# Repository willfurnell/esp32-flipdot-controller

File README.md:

# `esp32-flipdot-controller`

## Replacement controller for Hannover Flipdot Displays

This is a fork of the original https://github.com/themainframe/esp32-flipdot-controller, but is designed to allow for more than one panel (my display has three), and works with the Platform.IO build, and Arduino ecosystems.

It currently gets the time from an NTP server and displays it. The code obviosuly needs more work, but it's good enough for now. 

Also included in this repository are KiCad schematics for my version of the PCB, which has hardware (but not yet software) support for the built in LED strip and other personal customisations.

Based on the [blog post on damow.net](https://damow.net/fun-with-flip-dot-displays/)!

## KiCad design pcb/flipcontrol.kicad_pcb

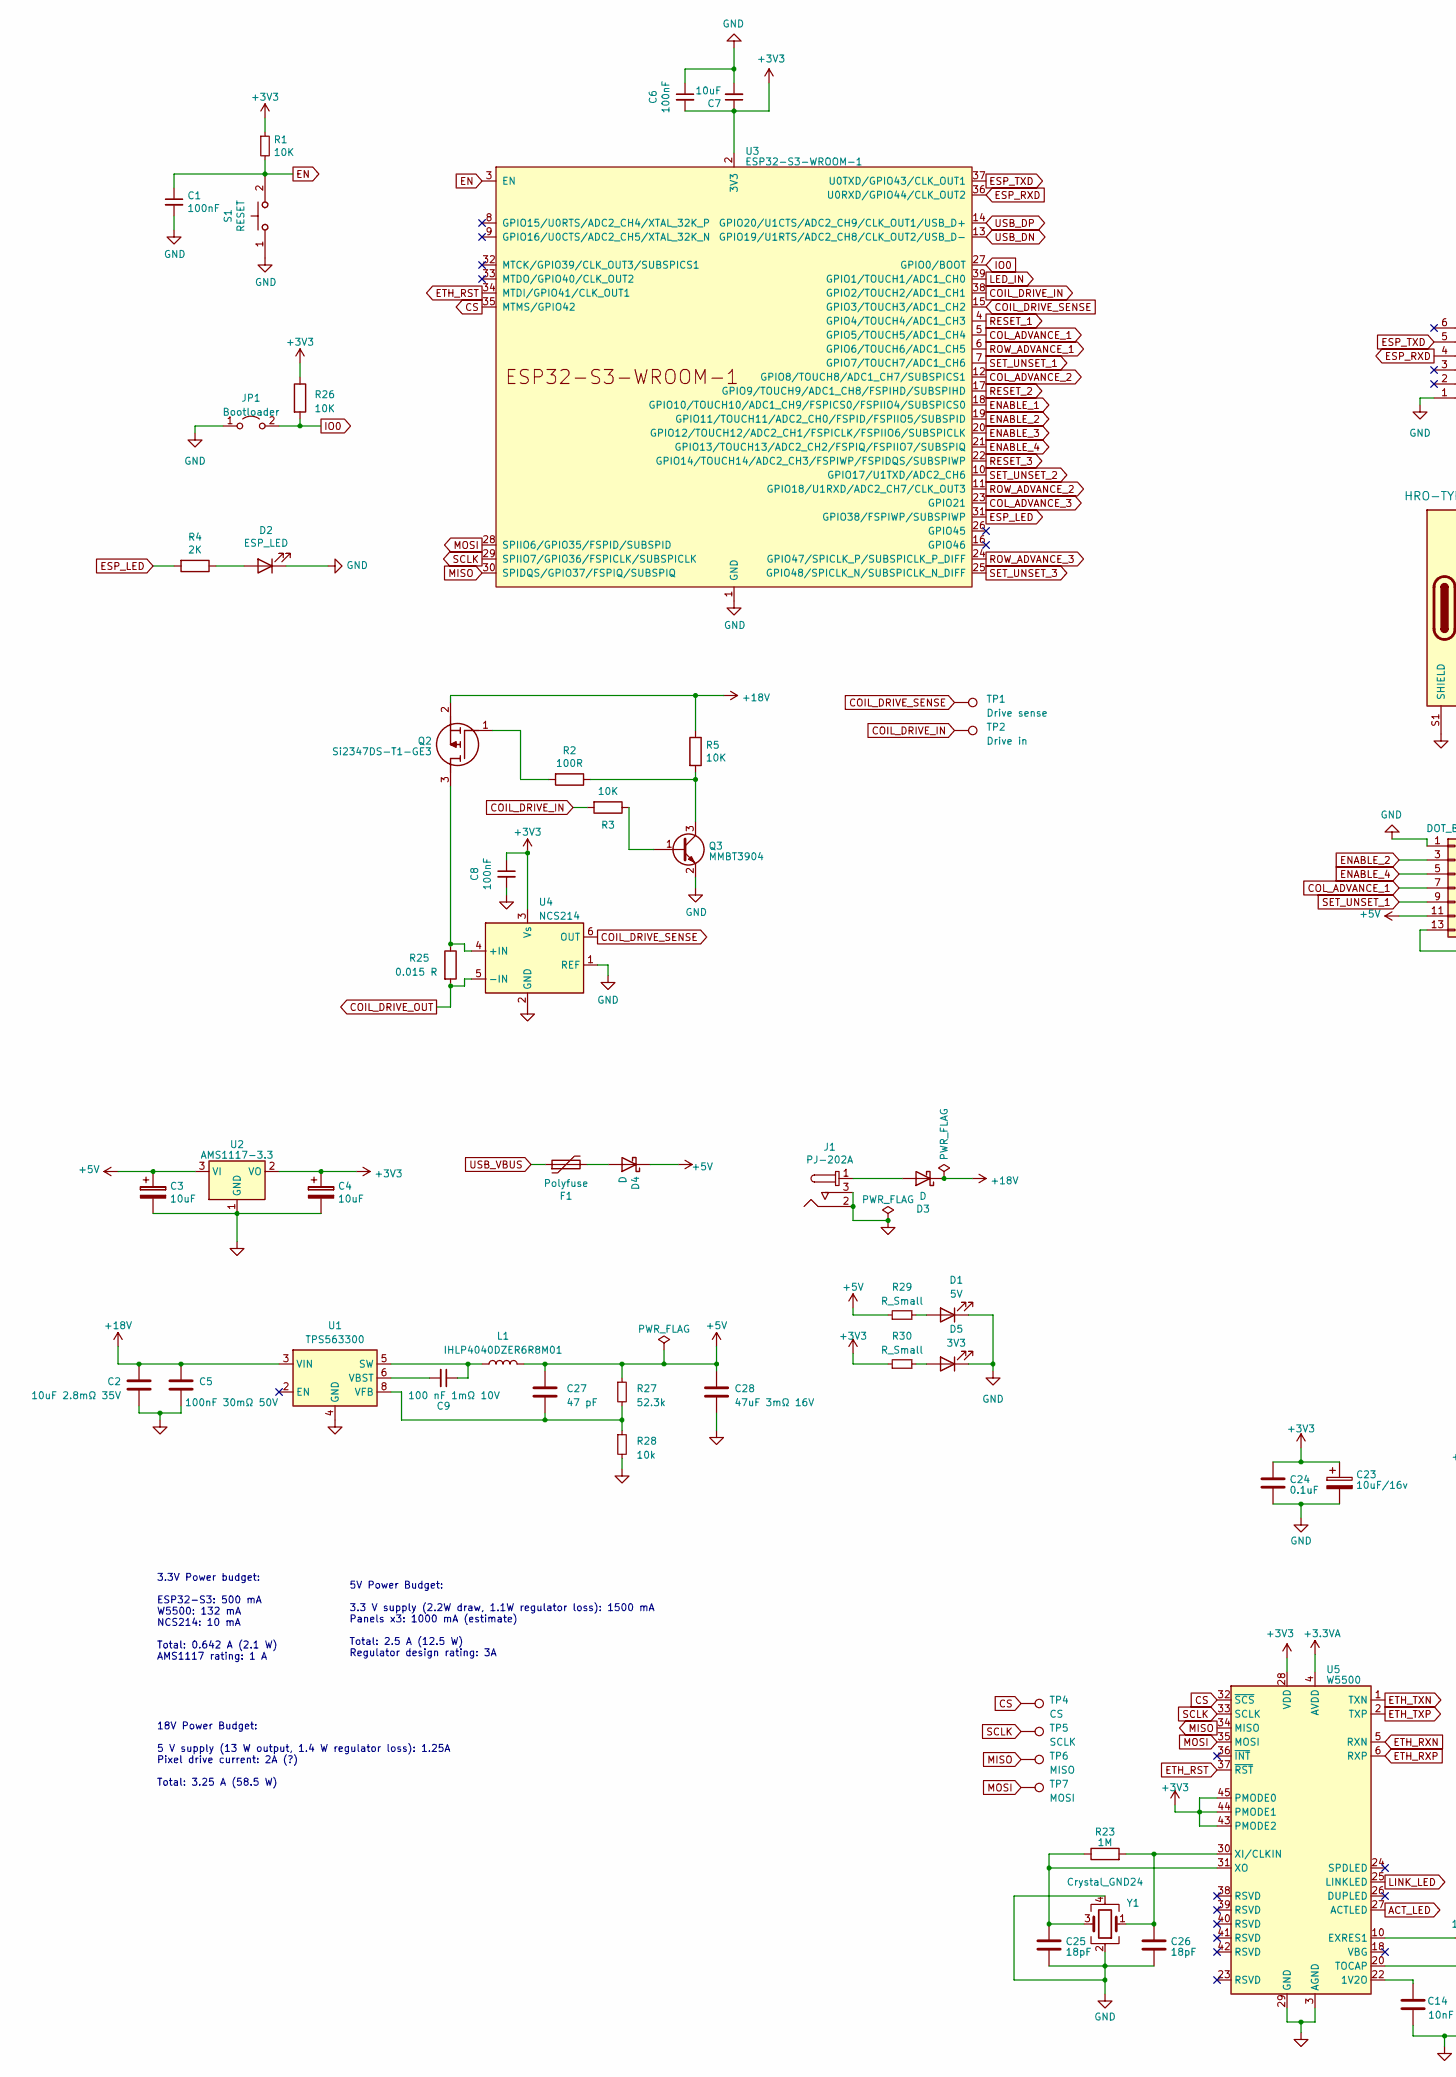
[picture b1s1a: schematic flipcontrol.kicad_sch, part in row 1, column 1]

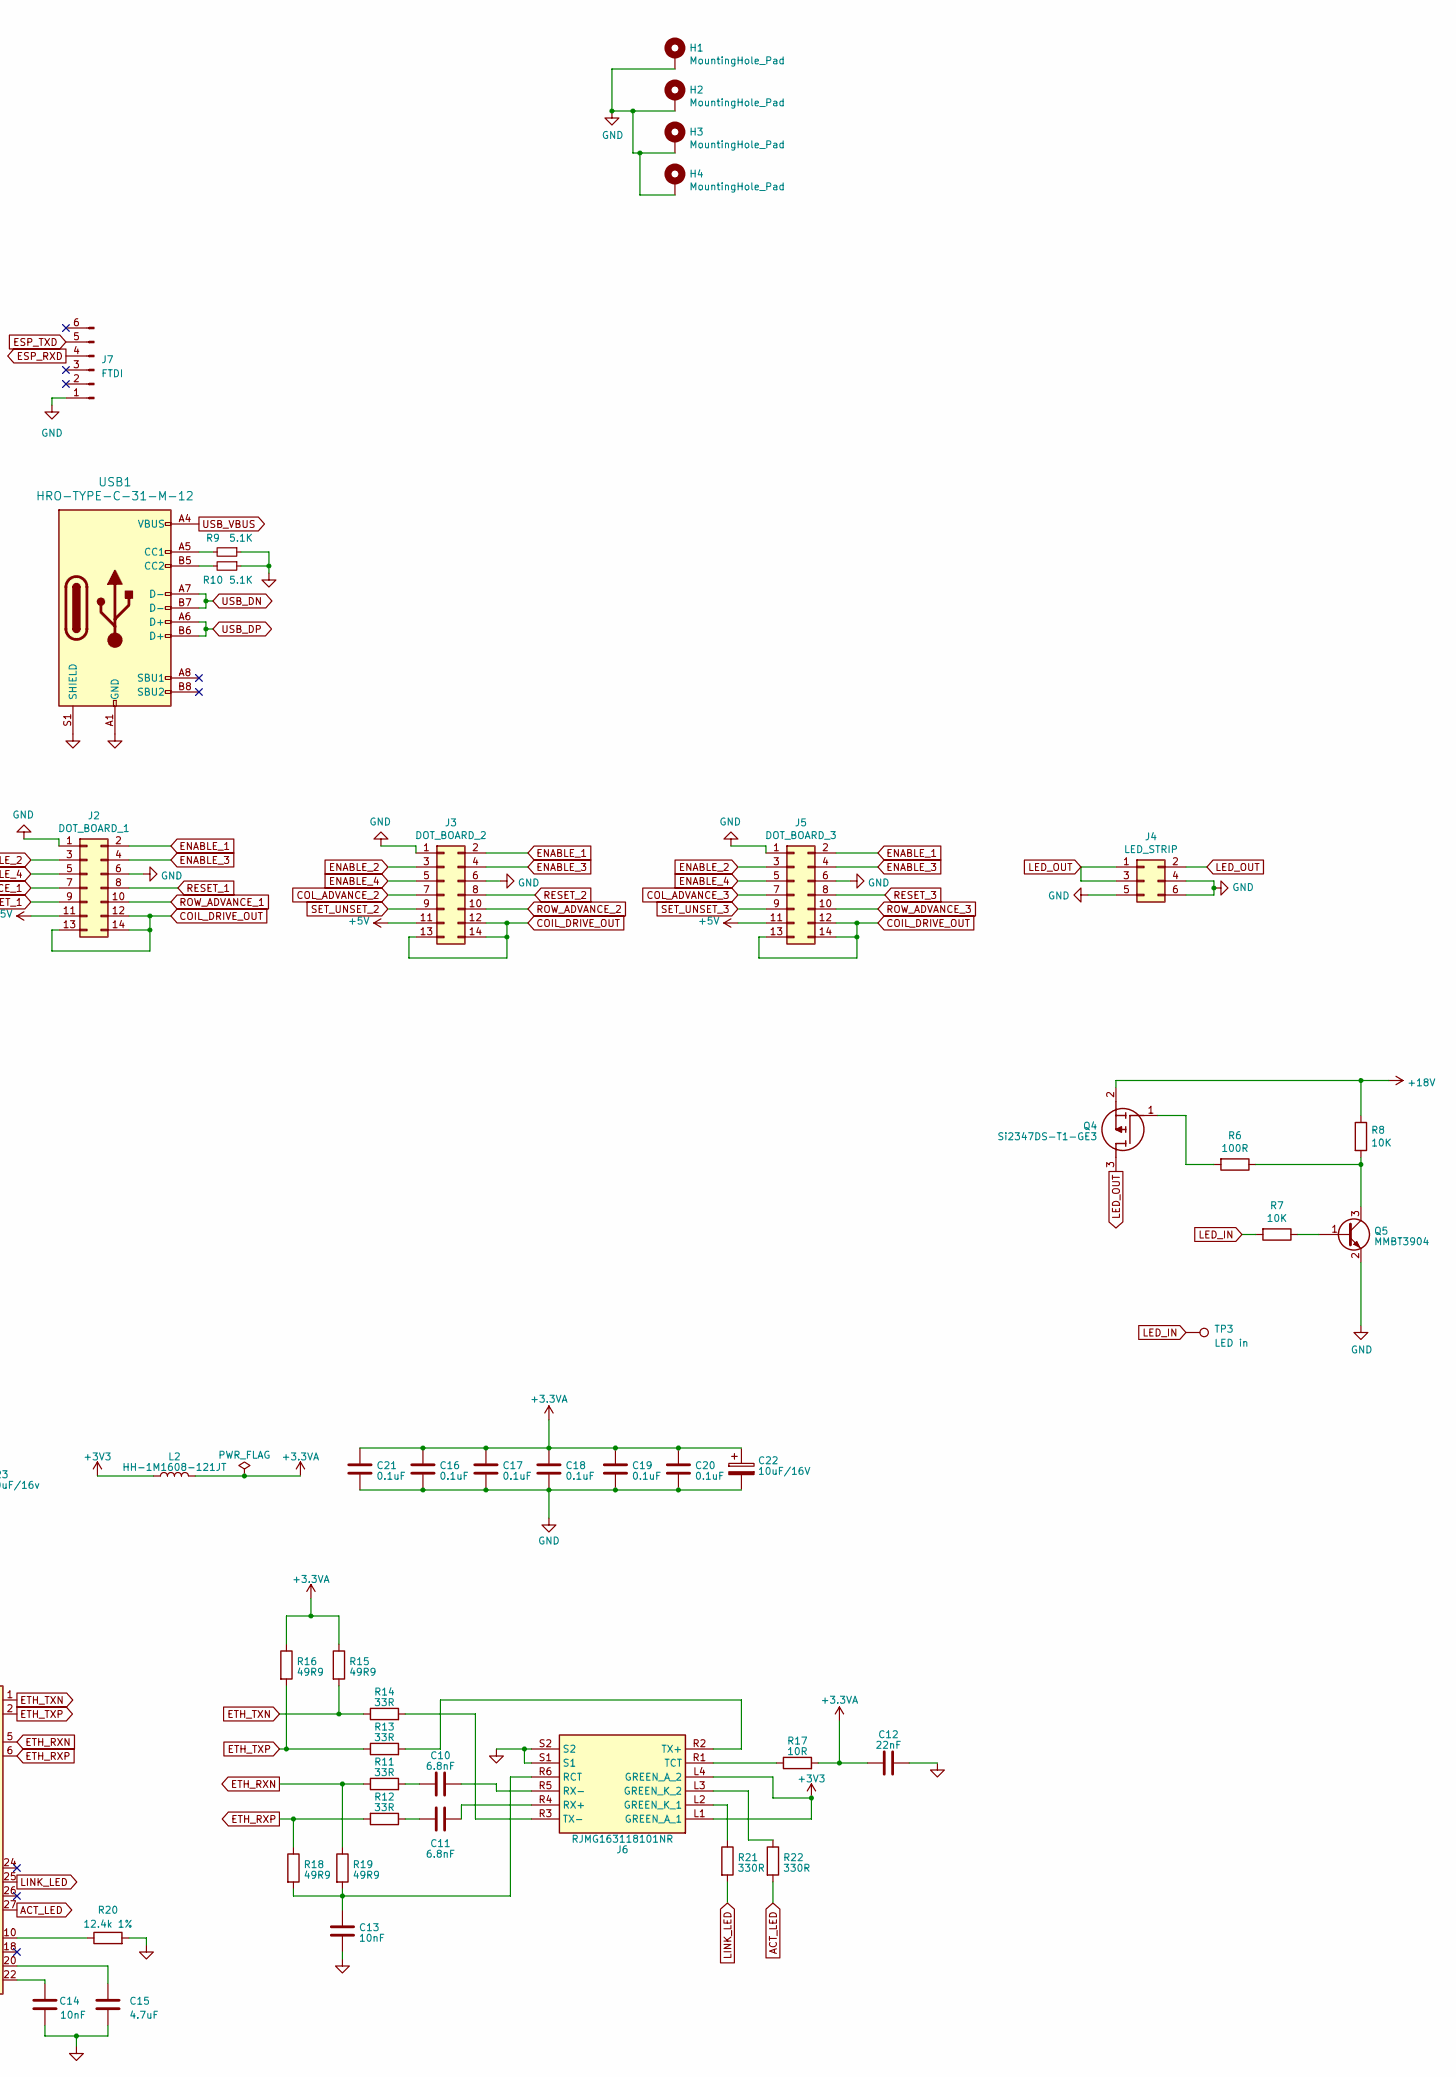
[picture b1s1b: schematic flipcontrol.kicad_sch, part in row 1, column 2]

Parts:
C1, C6, C8: 100nF; C_0805_2012Metric
C2: 10uF 2.8mΩ 35V; C_0805_2012Metric
C3, C4, C7: 10uF; C_0805_2012Metric
C5: 100nF 30mΩ 50V; C_0805_2012Metric
C9: 100 nF 1mΩ 10V; C_0805_2012Metric
C10, C11: 6.8nF; C_0805_2012Metric
C12: 22nF; C_0805_2012Metric
C13, C14: 10nF; C_0805_2012Metric
C15: 4.7uF; C_0805_2012Metric
C16, C17, C18, C19, C20, C21, C24: 0.1uF; C_0805_2012Metric
C22: 10uF/16V; C_0805_2012Metric
C23: 10uF/16v; C_0805_2012Metric
C25, C26: 18pF; C_0805_2012Metric
C27: 47 pF; C_0805_2012Metric
C28: 47uF 3mΩ 16V; C_1210_3225Metric
D1: 5V; LED_0805_2012Metric
D2: ESP_LED; LED_0805_2012Metric
D3, D4: D; D_SOD-123
D5: 3V3; LED_0805_2012Metric
F1: Polyfuse; Fuse_1206_3216Metric
H1, H2, H3, H4: MountingHole_Pad; MountingHole_5.3mm_M5_Pad
J1: PJ-202A; Barrel_Jack_5.5mmODx2.1mmID_PJ-202A; MPN PJ-202A; Digi-Key_PN CP-202A-ND
J2: DOT_BOARD_1; IDC-Header_2x07_P2.54mm_Vertical
J3: DOT_BOARD_2; IDC-Header_2x07_P2.54mm_Vertical
J4: LED_STRIP; IDC-Header_2x03_P2.54mm_Vertical
J5: DOT_BOARD_3; IDC-Header_2x07_P2.54mm_Vertical
J6: RJMG163118101NR; Manufacturer_Part_Number RJMG163118101NR; Mouser Part Number 523-RJMG163118101NR
J7: FTDI; PinHeader_1x06_P2.54mm_Vertical
JP1: Bootloader; Jumper_Tin_P5.32mm
L1: IHLP4040DZER6R8M01; L_Vishay_IHLP-4040
L2: HH-1M1608-121JT; L_0805_2012Metric
Q2, Q4: Si2347DS-T1-GE3; SOT95P237X112-3N; Manufacturer_Part_Number Si2347DS-T1-GE3; Mouser Part Number 78-SI2347DS-T1-GE3
Q3, Q5: MMBT3904; SOT-23
R1, R3, R5, R7, R8, R26: 10K; R_0805_2012Metric
R2, R6: 100R; R_0805_2012Metric
R4: 2K; R_0805_2012Metric
R9, R10: 5.1K; R_0805_2012Metric
R11, R12, R13, R14: 33R; R_0805_2012Metric
R15, R16, R18, R19: 49R9; R_0805_2012Metric
R17: 10R; R_0805_2012Metric
R20: 12.4k 1%; R_0805_2012Metric
R21, R22: 330R; R_0805_2012Metric
R23: 1M; R_0805_2012Metric
R25: 0.015 R; R_0805_2012Metric
R27: 52.3k; R_0805_2012Metric
R28: 10k; R_0805_2012Metric
R29, R30: R_Small; R_0805_2012Metric
S1: RESET; FSM2JRT; Mouser Part Number 506-FSM2JRT
TP1: Drive sense; TestPoint_Pad_D2.0mm
TP2: Drive in; TestPoint_Pad_D2.0mm
TP3: LED in; TestPoint_Pad_D2.0mm
TP4: CS; TestPoint_Pad_D2.0mm
TP5: SCLK; TestPoint_Pad_D2.0mm
TP6: MISO; TestPoint_Pad_D2.0mm
TP7: MOSI; TestPoint_Pad_D2.0mm
U1: TPS563300; SOT-583-8
U2: AMS1117-3.3; SOT-223-3_TabPin2
U3: ESP32-S3-WROOM-1
U4: NCS214; SOT-363_SC-70-6_Handsoldering
U5: W5500; LQFP-48_7x7mm_P0.5mm
USB1: HRO-TYPE-C-31-M-12; USB_C_Receptacle_HRO_TYPE-C-31-M-12
Y1: Crystal_GND24; Crystal_SMD_Abracon_ABM8G-4Pin_3.2x2.5mm

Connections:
+3.3VA: C12.1, C16.1, C17.1, C18.1, C19.1, C20.1, C21.1, C22.1, L2.2, R15.1, R16.1, R17.2, U5.4 (AVDD), U5.8 (AVDD), U5.11 (AVDD), U5.15 (AVDD), U5.17 (AVDD), U5.21 (AVDD)
+3V3: C4.1, C6.2, C7.1, C8.1, C23.1, C24.1, J6.L1 (GREEN_A_1), J6.L4 (GREEN_A_2), L2.1, R1.1, R26.1, R30.1, U2.2 (VO), U3.2 (3V3), U4.3 (Vs), U5.28 (VDD), U5.43 (PMODE2), U5.44 (PMODE1), U5.45 (PMODE0)
+5V: C3.1, C27.1, C28.1, D4.1 (K), J2.11, J3.11, J5.11, L1.2, R27.1, R29.1, U2.3 (VI)
+18V: C2.1, C5.1, D3.1 (K), Q2.2 (S), Q4.2 (S), R5.1, R8.1, U1.3 (VIN)
ACT_LED: R22.2, U5.27 (ACTLED)
COIL_DRIVE_IN: R3.2, TP2.1, U3.38 (GPIO2/TOUCH2/ADC1_CH1)
COIL_DRIVE_OUT: J2.12, J2.13, J2.14, J3.12, J3.13, J3.14, J5.12, J5.13, J5.14, R25.2, U4.5 (-IN)
COIL_DRIVE_SENSE: TP1.1, U3.15 (GPIO3/TOUCH3/ADC1_CH2), U4.6 (OUT)
COL_ADVANCE_1: J2.7, U3.5 (GPIO5/TOUCH5/ADC1_CH4)
COL_ADVANCE_2: J3.7, U3.12 (GPIO8/TOUCH8/ADC1_CH7/SUBSPICS1)
COL_ADVANCE_3: J5.7, U3.23 (GPIO21)
CS: TP4.1, U3.35 (MTMS/GPIO42), U5.32 (~SCS)
EN: C1.1, R1.2, S1.2, U3.3 (EN)
ENABLE_1: J2.2, J3.2, J5.2, U3.18 (GPIO10/TOUCH10/ADC1_CH9/FSPICS0/FSPIIO4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)
ENABLE_2: J2.3, J3.3, J5.3, U3.19 (GPIO11/TOUCH11/ADC2_CH0/FSPID/FSPIIO5/S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)
ENABLE_3: J2.4, J3.4, J5.4, U3.20 (GPIO12/TOUCH12/ADC2_CH1/FSPICLK/FSPIIO6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)
ENABLE_4: J2.5, J3.5, J5.5, U3.21 (GPIO13/TOUCH13/ADC2_CH2/FSPIQ/FSPIIO7/S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)
ESP_LED: R4.2, U3.31 (GPIO38/FSPIWP/SUBSPIWP)
ESP_RXD: J7.4, U3.36 (U0RXD/GPIO44/CLK_OUT2)
ESP_TXD: J7.5, U3.37 (U0TXD/GPIO43/CLK_OUT1)
ETH_RST: U3.34 (MTDI/GPIO41/CLK_OUT1), U5.37 (~RST)
ETH_RXN: R11.1, R19.1, U5.5 (RXN)
ETH_RXP: R12.2, R18.1, U5.6 (RXP)
ETH_TXN: R14.1, R15.2, U5.1 (TXN)
ETH_TXP: R13.1, R16.2, U5.2 (TXP)
GND: C1.2, C2.2, C3.2, C4.2, C5.2, C6.1, C7.2, C8.2, C12.2, C13.2, C14.1, C15.1, C16.2, C17.2, C18.2, C19.2, C20.2, C21.2, C22.2, C23.2, C24.2, C25.2, C26.2, C28.2, D1.1 (K), D2.1 (K), D5.1 (K), H1.1, H2.1, H3.1, H4.1, J1.2, J1.3, J2.1, J2.6, J3.1, J3.6, J4.4, J4.5, J4.6, J5.1, J5.6, J6.S1, J6.S2, J7.1, JP1.1 (A), Q3.2 (E), Q5.2 (E), R9.1, R10.1, R20.2, R28.2, S1.1, U1.4 (GND), U2.1 (GND), U3.1 (GND), U3.40 (GND), U3.41 (GND), U4.1 (REF), U4.2 (GND), U5.3 (AGND), U5.9 (AGND), U5.14 (AGND), U5.16 (AGND), U5.19 (AGND), U5.29 (GND), U5.48 (AGND), USB1.A1 (GND), USB1.A12 (GND), USB1.B1 (GND), USB1.B12 (GND), USB1.S1 (SHIELD), Y1.2, Y1.4
IO0: JP1.2 (B), R26.2, U3.27 (GPIO0/BOOT)
LED_IN: R7.2, TP3.1, U3.39 (GPIO1/TOUCH1/ADC1_CH0)
LED_OUT: J4.1, J4.2, J4.3, Q4.3 (D)
LINK_LED: R21.2, U5.25 (LINKLED)
MISO: TP6.1, U3.30 (SPIDQS/GPIO37/FSPIQ/SUBSPIQ), U5.34 (MISO)
MOSI: TP7.1, U3.28 (SPIIO6/GPIO35/FSPID/SUBSPID), U5.35 (MOSI)
unnamed: C10.2, R11.2
unnamed: C11.1, R12.1
unnamed: D1.2 (A), R29.2
unnamed: D2.2 (A), R4.1
unnamed: D3.2 (A), J1.1
unnamed: D4.2 (A), F1.2
unnamed: D5.2 (A), R30.2
unnamed: J6.L2 (GREEN_K_1), R21.1
unnamed: J6.L3 (GREEN_K_2), R22.1
unnamed: C13.1, J6.R6 (RCT), R18.2, R19.2
unnamed: C11.2, J6.R4 (RX+)
unnamed: C10.1, J6.R5 (RX-)
unnamed: J6.R1 (TCT), R17.1
unnamed: J6.R2 (TX+), R13.2
unnamed: J6.R3 (TX-), R14.2
unnamed: Q2.3 (D), R25.1, U4.4 (+IN)
unnamed: Q2.1 (G), R2.2
unnamed: Q3.1 (B), R3.1
unnamed: Q3.3 (C), R2.1, R5.2
unnamed: Q4.1 (G), R6.2
unnamed: Q5.1 (B), R7.1
unnamed: Q5.3 (C), R6.1, R8.2
unnamed: C9.1, L1.1, U1.5 (SW)
unnamed: C9.2, U1.6 (VBST)
unnamed: C27.2, R27.2, R28.1, U1.8 (VFB)
unnamed: C14.2, U5.22 (1V2O)
unnamed: R20.1, U5.10 (EXRES1)
unnamed: C15.2, U5.20 (TOCAP)
unnamed: C26.1, R23.2, U5.30 (XI/CLKIN), Y1.1
unnamed: C25.1, R23.1, U5.31 (XO), Y1.3
unnamed: R9.2, USB1.A5 (CC1)
unnamed: R10.2, USB1.B5 (CC2)
RESET_1: J2.8, U3.4 (GPIO4/TOUCH4/ADC1_CH3)
RESET_2: J3.8, U3.17 (GPIO9/TOUCH9/ADC1_CH8/FSPIHD/SUBSPIHD)
RESET_3: J5.8, U3.22 (GPIO14/TOUCH14/ADC2_CH3/FSPIWP/FSPIDQS/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)
ROW_ADVANCE_1: J2.10, U3.6 (GPIO6/TOUCH6/ADC1_CH5)
ROW_ADVANCE_2: J3.10, U3.11 (GPIO18/U1RXD/ADC2_CH7/CLK_OUT3)
ROW_ADVANCE_3: J5.10, U3.24 (GPIO47/SPICLK_P/SUBSPICLK_P_DIFF)
SCLK: TP5.1, U3.29 (SPIIO7/GPIO36/FSPICLK/SUBSPICLK), U5.33 (SCLK)
SET_UNSET_1: J2.9, U3.7 (GPIO7/TOUCH7/ADC1_CH6)
SET_UNSET_2: J3.9, U3.10 (GPIO17/U1TXD/ADC2_CH6)
SET_UNSET_3: J5.9, U3.25 (GPIO48/SPICLK_N/SUBSPICLK_N_DIFF)
USB_DN: U3.13 (GPIO19/U1RTS/ADC2_CH8/CLK_OUT2/USB_D-), USB1.A7 (D-), USB1.B7 (D-)
USB_DP: U3.14 (GPIO20/U1CTS/ADC2_CH9/CLK_OUT1/USB_D+), USB1.A6 (D+), USB1.B6 (D+)
USB_VBUS: F1.1, USB1.A4 (VBUS), USB1.A9 (VBUS), USB1.B4 (VBUS), USB1.B9 (VBUS)

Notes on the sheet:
3.3V Power budget: ESP32-S3: 500 mA W5500: 132 mA NCS214: 10 mA Total: 0.642 A (2.1 W) AMS1117 rating: 1 A
18V Power Budget: 5 V supply (13 W output, 1.4 W regulator loss): 1.25A Pixel drive current: 2A (?) Total: 3.25 A (58.5 W)
5V Power Budget: 3.3 V supply (2.2W draw, 1.1W regulator loss): 1500 mA Panels x3: 1000 mA (estimate) Total: 2.5 A (12.5 W) Regulator design rating: 3A

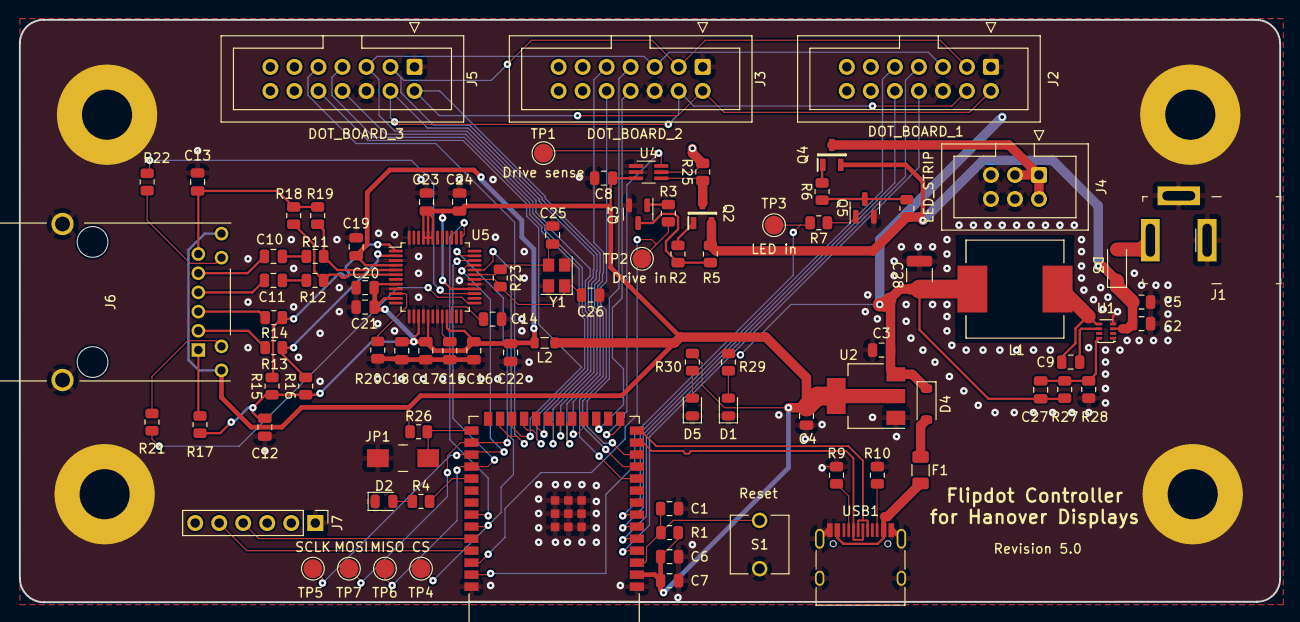
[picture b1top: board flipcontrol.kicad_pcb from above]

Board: 4 copper layers, 133.3 x 61.6 mm, 96 parts (0 on the bottom side), 77 nets.

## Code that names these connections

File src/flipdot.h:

#ifndef FLIPDOT_H
#define FLIPDOT_H

#include <stdint.h>
#include <stdbool.h>

// Dimensions of your display
//#define DOT_ROWS 8
//#define DOT_COLUMNS 84
//#define NUM_PANELS 3
//#define COLUMNS_PER_PANEL 28

// 32 x 16

#define DOT_ROWS 16
#define DOT_COLUMNS 96
#define NUM_PANELS 3
#define COLUMNS_PER_PANEL 32


// GPIO Pin Definitions
//#define PIN_ENABLE_1 GPIO_NUM_12
//#define PIN_ENABLE_2 GPIO_NUM_13
//#define PIN_ENABLE_3 GPIO_NUM_14
//#define PIN_ENABLE_4 GPIO_NUM_15
//#define PIN_COLUMN_ADVANCE GPIO_NUM_17
//#define PIN_RESET GPIO_NUM_16
//#define PIN_SET_UNSET GPIO_NUM_19
//#define PIN_ROW_ADVANCE GPIO_NUM_18
//#define PIN_COIL_DRIVE GPIO_NUM_21

#define PIN_ENABLE_1 GPIO_NUM_10
#define PIN_ENABLE_2 GPIO_NUM_11
#define PIN_ENABLE_3 GPIO_NUM_12
#define PIN_ENABLE_4 GPIO_NUM_13
#define PIN_COLUMN_ADVANCE GPIO_NUM_5
#define PIN_RESET GPIO_NUM_4
#define PIN_SET_UNSET GPIO_NUM_7
#define PIN_ROW_ADVANCE GPIO_NUM_6
#define PIN_COIL_DRIVE GPIO_NUM_2

#define GPIO_OUTPUT_PIN_SEL ((1ULL << PIN_ENABLE_1) | (1ULL << PIN_ENABLE_2) | (1ULL << PIN_ENABLE_3) | (1ULL << PIN_ENABLE_4) | (1ULL << PIN_COLUMN_ADVANCE) | (1ULL << PIN_RESET) | (1ULL << PIN_SET_UNSET) | (1ULL << PIN_ROW_ADVANCE) | (1ULL << PIN_COIL_DRIVE))

// Cycle count in 1 µS
#define CYCLES_PER_US 600

// Timings (µS)
#define PULSE_TIME_US 200
#define WAIT_TIME 1

// Types
typedef uint8_t dotboard_t[DOT_COLUMNS][DOT_ROWS];

// Public subs
void flipdot_init();
void write_dotboard(dotboard_t *dots, bool is_keyframe);

#endif

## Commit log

2020-10-11 Convert to platform.io
2020-10-11 Update to work with more than one panel (in this case three)
2020-10-11 Autoformat code for readability
2020-10-11 Allow configuration of display panels
2020-10-11 Add PCB files
2023-04-21 Update for Kicad 7, update some components
2023-04-22 Update schematic with newer parts
2023-04-22 Update PCB
2023-04-23 Update with latest schematic and board changes
2023-04-23 Update .gitignore with new KiCad bits
2023-04-23 Add libraries submodule
2023-04-23 Add required kicad parts straight into this repo
2023-04-23 Start work on Ethernet support in schematic
2023-04-25 Finish adding Ethernet interface
2023-04-29 Remove old KiCAD v6 project files
2023-05-06 Add footprints for all parts
2023-05-07 Schematic update
    * Remove USB-serial chip, use ESP32's USB support
    * Add serial header and bootloader jumper in case that doesn't work
    * Add drive current sensing
    * ERC tidyup
    * Add a few test points for good measure
2023-05-08 Rework schematic:
    New 5V regulator design, use ESP32's native USB and add FTDI header,
    misc other improvements
2023-05-08 PCB layout
2023-05-08 Fix board being ever so slightly off square
2023-05-08 Remove gerbers folder
2023-05-11 Make panel pin 14 constantly powered with 18V
2023-05-13 Add kibot action
2023-05-13 Trigger kibot action on change to action yml
2023-05-13 Fix kibot yml file name
2023-05-13 Fix trigger paths
2023-05-13 Explicitly set paths
2023-05-13 Use dev kibot version
2023-05-13 Use dev version of kibot
2023-05-14 Remove broken kibot targets, remove BOM file
2023-05-14 Fix workflow file
2023-05-14 Schematic updates to improve component values
2023-11-28 Show ghost or cyberman graphics, and more information when booting
2023-11-28 Update PCB to use more JLCPCB parts for power supply
2024-02-04 Properly deal with multi panel boards
2024-02-04 Add new env for rev3 boards
2024-09-12 Rev4: Make more parts JLCPCB assembly service compatible
2025-01-05 Convert to 8.99, latest work for transfer to desktop PC
2025-02-15 JLCPB parts update
